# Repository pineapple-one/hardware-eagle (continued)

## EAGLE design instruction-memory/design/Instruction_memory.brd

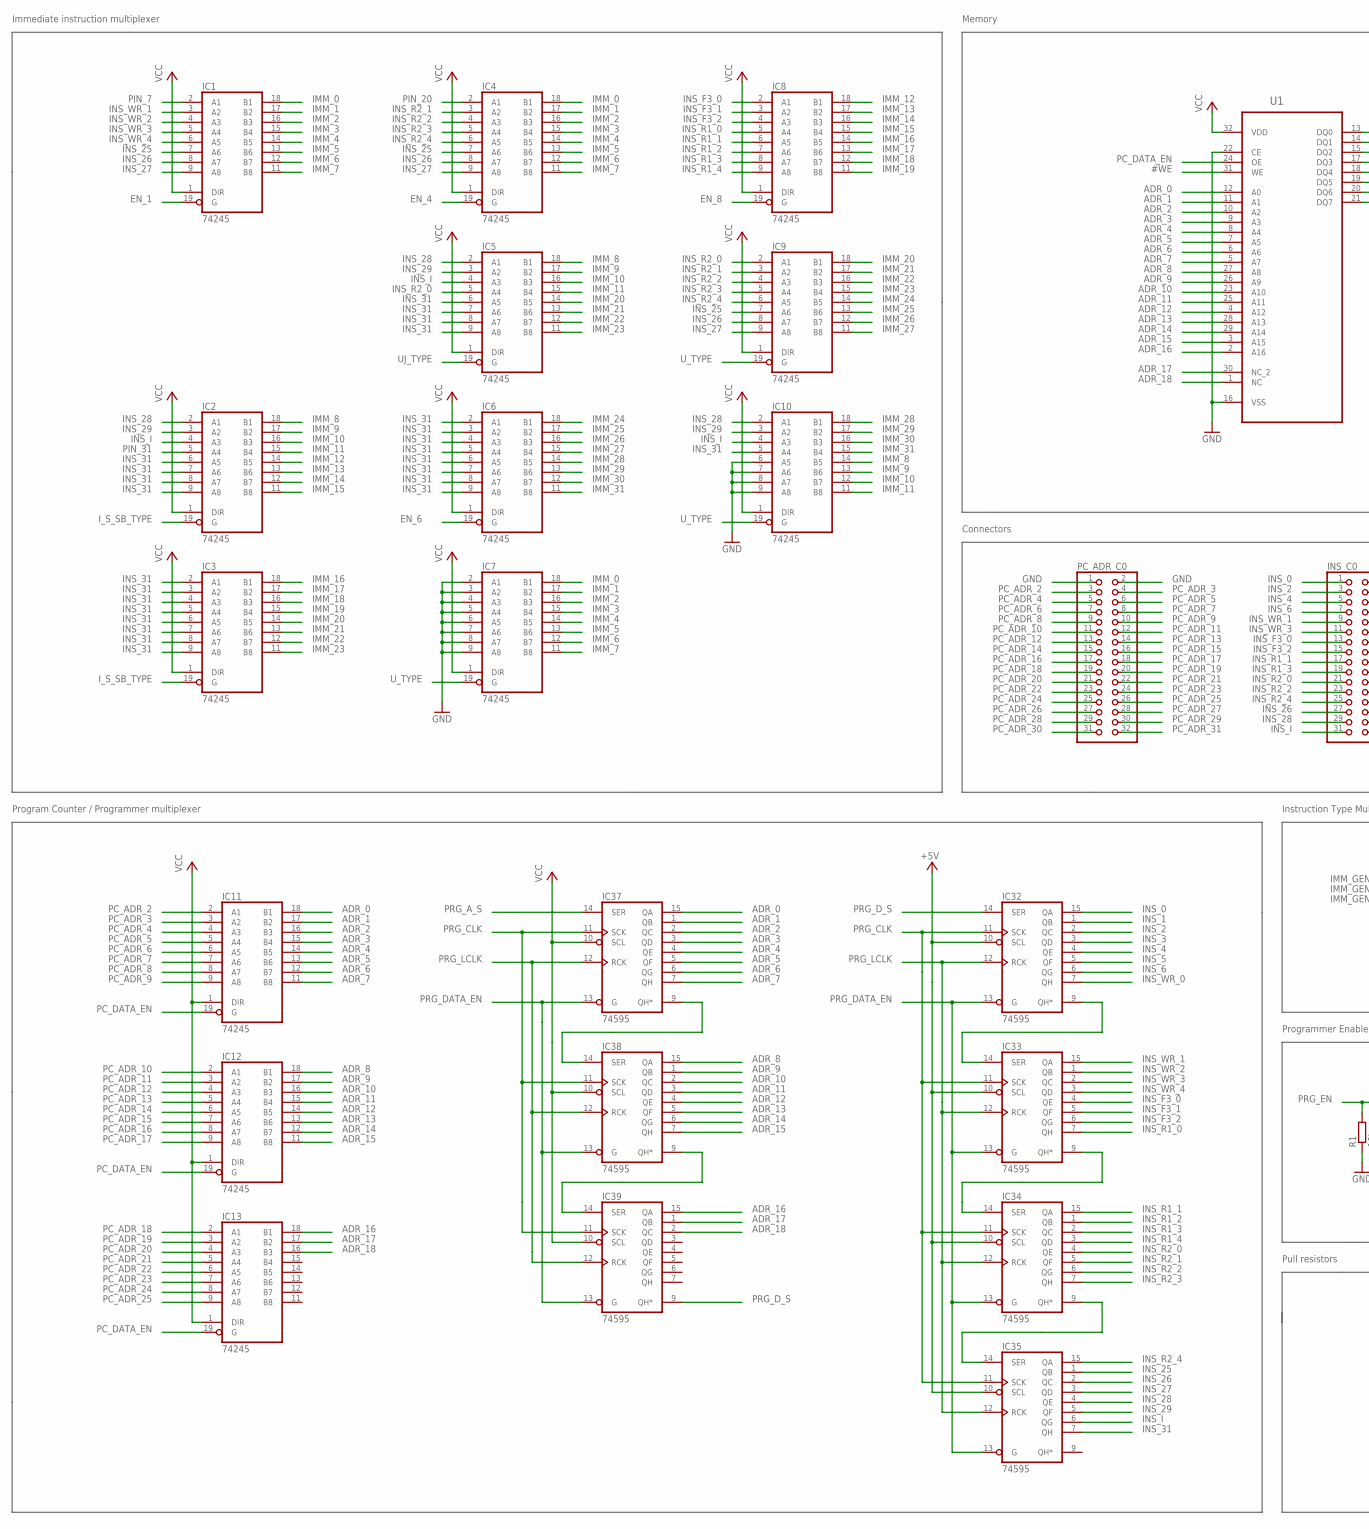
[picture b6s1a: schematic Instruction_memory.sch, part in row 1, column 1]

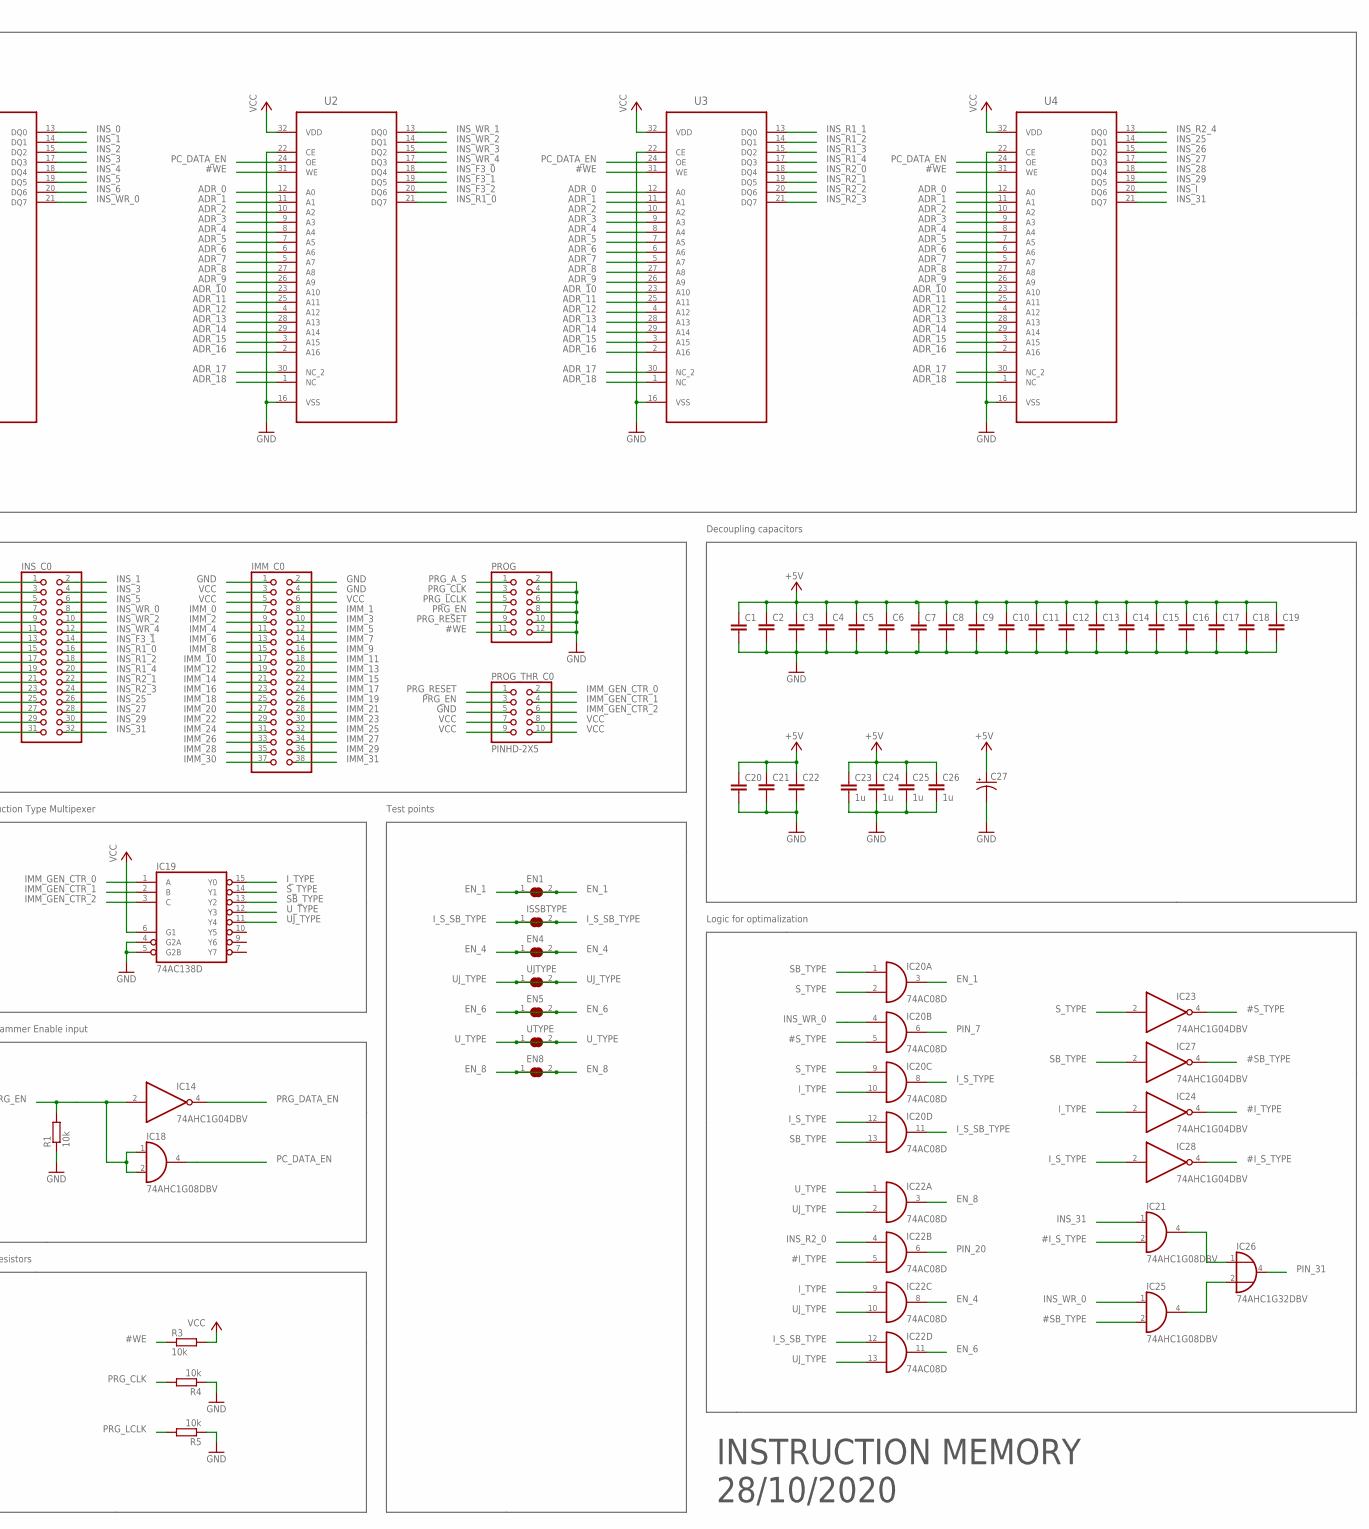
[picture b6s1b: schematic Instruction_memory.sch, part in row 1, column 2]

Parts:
C1, C2, C3, C4, C5, C6, C7, C8, C9, C10, C11, C12, C13, C14, C15, C16, C17, C18, C19, C20, C21, C22: C-EUC0805; C0805
C23, C24, C25, C26: 1u; C0805
C27: CAPACITOR-P153CLV-1010; 153CLV-1010
EN1, EN4, EN5, EN8: SJ
IC1, IC2, IC3, IC4, IC5, IC6, IC7, IC8, IC9, IC10, IC11, IC12, IC13: 74245; TSSOP20
IC14, IC23, IC24, IC27, IC28: 74AHC1G04DBV; SOT23-5
IC18, IC21, IC25: 74AHC1G08DBV; SOT23-5
IC19: 74AC138D; SO16
IC20, IC22: 74AC08D; SO14
IC26: 74AHC1G32DBV; SOT23-5
IC32, IC33, IC34, IC35, IC37, IC38, IC39: 74595; TSSOP16
IMM_C0: PINHD-2X19; 2X19
INS_C0: PINHD-2X16; 2X16
ISSBTYPE: SJ
PC_ADR_C0: PINHD-2X16; 2X16
PROG: PINHD-2X6; 2X06
PROG_THR_C0: PINHD-2X5; 2X05
R1, R3, R4, R5: 10k; R0805
U1, U2, U3, U4: SST39SF010A-70-4I-NHEPLCC32; S32
UJTYPE: SJ
UTYPE: SJ

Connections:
#I_S_TYPE: IC21.2 (I1), IC28.4 (O)
#I_TYPE: IC22.5 (I1), IC24.4 (O)
#SB_TYPE: IC25.2 (I1), IC27.4 (O)
#S_TYPE: IC20.5 (I1), IC23.4 (O)
#WE: PROG.11, R3.1, U1.31 (WE), U2.31 (WE), U3.31 (WE), U4.31 (WE)
ADR_0: IC11.18 (B1), IC37.15 (QA), U1.12 (A0), U2.12 (A0), U3.12 (A0), U4.12 (A0)
ADR_1: IC11.17 (B2), IC37.1 (QB), U1.11 (A1), U2.11 (A1), U3.11 (A1), U4.11 (A1)
ADR_2: IC11.16 (B3), IC37.2 (QC), U1.10 (A2), U2.10 (A2), U3.10 (A2), U4.10 (A2)
ADR_3: IC11.15 (B4), IC37.3 (QD), U1.9 (A3), U2.9 (A3), U3.9 (A3), U4.9 (A3)
ADR_4: IC11.14 (B5), IC37.4 (QE), U1.8 (A4), U2.8 (A4), U3.8 (A4), U4.8 (A4)
ADR_5: IC11.13 (B6), IC37.5 (QF), U1.7 (A5), U2.7 (A5), U3.7 (A5), U4.7 (A5)
ADR_6: IC11.12 (B7), IC37.6 (QG), U1.6 (A6), U2.6 (A6), U3.6 (A6), U4.6 (A6)
ADR_7: IC11.11 (B8), IC37.7 (QH), U1.5 (A7), U2.5 (A7), U3.5 (A7), U4.5 (A7)
ADR_8: IC12.18 (B1), IC38.15 (QA), U1.27 (A8), U2.27 (A8), U3.27 (A8), U4.27 (A8)
ADR_9: IC12.17 (B2), IC38.1 (QB), U1.26 (A9), U2.26 (A9), U3.26 (A9), U4.26 (A9)
ADR_10: IC12.16 (B3), IC38.2 (QC), U1.23 (A10), U2.23 (A10), U3.23 (A10), U4.23 (A10)
ADR_11: IC12.15 (B4), IC38.3 (QD), U1.25 (A11), U2.25 (A11), U3.25 (A11), U4.25 (A11)
ADR_12: IC12.14 (B5), IC38.4 (QE), U1.4 (A12), U2.4 (A12), U3.4 (A12), U4.4 (A12)
ADR_13: IC12.13 (B6), IC38.5 (QF), U1.28 (A13), U2.28 (A13), U3.28 (A13), U4.28 (A13)
ADR_14: IC12.12 (B7), IC38.6 (QG), U1.29 (A14), U2.29 (A14), U3.29 (A14), U4.29 (A14)
ADR_15: IC12.11 (B8), IC38.7 (QH), U1.3 (A15), U2.3 (A15), U3.3 (A15), U4.3 (A15)
ADR_16: IC13.18 (B1), IC39.15 (QA), U1.2 (A16), U2.2 (A16), U3.2 (A16), U4.2 (A16)
ADR_17: IC13.17 (B2), IC39.1 (QB), U1.30 (NC_2), U2.30 (NC_2), U3.30 (NC_2), U4.30 (NC_2)
ADR_18: IC13.16 (B3), IC39.2 (QC), U1.1 (NC), U2.1 (NC), U3.1 (NC), U4.1 (NC)
EN_1: EN1.1, EN1.2, IC1.19 (G), IC20.3 (O)
EN_4: EN4.1, EN4.2, IC4.19 (G), IC22.8 (O)
EN_6: EN5.1, EN5.2, IC6.19 (G), IC22.11 (O)
EN_8: EN8.1, EN8.2, IC8.19 (G), IC22.3 (O)
GND: C1.2, C2.2, C3.2, C4.2, C5.2, C6.2, C7.2, C8.2, C9.2, C10.2, C11.2, C12.2, C13.2, C14.2, C15.2, C16.2, C17.2, C18.2, C19.2, C20.2, C21.2, C22.2, C23.2, C24.2, C25.2, C26.2, C27.-, IC1.10 (GND), IC2.10 (GND), IC3.10 (GND), IC4.10 (GND), IC5.10 (GND), IC6.10 (GND), IC7.2 (A1), IC7.3 (A2), IC7.4 (A3), IC7.5 (A4), IC7.6 (A5), IC7.7 (A6), IC7.8 (A7), IC7.9 (A8), IC7.10 (GND), IC8.10 (GND), IC9.10 (GND), IC10.6 (A5), IC10.7 (A6), IC10.8 (A7), IC10.9 (A8), IC10.10 (GND), IC11.10 (GND), IC12.10 (GND), IC13.10 (GND), IC14.3 (GND), IC18.3 (GND), IC19.4 (G2A), IC19.5 (G2B), IC19.8 (GND), IC20.7 (GND), IC21.3 (GND), IC22.7 (GND), IC23.3 (GND), IC24.3 (GND), IC25.3 (GND), IC26.3 (GND), IC27.3 (GND), IC28.3 (GND), IC32.8 (GND), IC33.8 (GND), IC34.8 (GND), IC35.8 (GND), IC37.8 (GND), IC38.8 (GND), IC39.8 (GND), IMM_C0.1, IMM_C0.2, IMM_C0.4, PC_ADR_C0.1, PC_ADR_C0.2, PROG.2, PROG.4, PROG.6, PROG.8, PROG.10, PROG.12, PROG_THR_C0.5, R1.1, R4.1, R5.1, U1.16 (VSS), U1.22 (CE), U2.16 (VSS), U2.22 (CE), U3.16 (VSS), U3.22 (CE), U4.16 (VSS), U4.22 (CE)
IMM_0: IC1.18 (B1), IC4.18 (B1), IC7.18 (B1), IMM_C0.7
IMM_1: IC1.17 (B2), IC4.17 (B2), IC7.17 (B2), IMM_C0.8
IMM_2: IC1.16 (B3), IC4.16 (B3), IC7.16 (B3), IMM_C0.9
IMM_3: IC1.15 (B4), IC4.15 (B4), IC7.15 (B4), IMM_C0.10
IMM_4: IC1.14 (B5), IC4.14 (B5), IC7.14 (B5), IMM_C0.11
IMM_5: IC1.13 (B6), IC4.13 (B6), IC7.13 (B6), IMM_C0.12
IMM_6: IC1.12 (B7), IC4.12 (B7), IC7.12 (B7), IMM_C0.13
IMM_7: IC1.11 (B8), IC4.11 (B8), IC7.11 (B8), IMM_C0.14
IMM_8: IC2.18 (B1), IC5.18 (B1), IC10.14 (B5), IMM_C0.15
IMM_9: IC2.17 (B2), IC5.17 (B2), IC10.13 (B6), IMM_C0.16
IMM_10: IC2.16 (B3), IC5.16 (B3), IC10.12 (B7), IMM_C0.17
IMM_11: IC2.15 (B4), IC5.15 (B4), IC10.11 (B8), IMM_C0.18
IMM_12: IC2.14 (B5), IC8.18 (B1), IMM_C0.19
IMM_13: IC2.13 (B6), IC8.17 (B2), IMM_C0.20
IMM_14: IC2.12 (B7), IC8.16 (B3), IMM_C0.21
IMM_15: IC2.11 (B8), IC8.15 (B4), IMM_C0.22
IMM_16: IC3.18 (B1), IC8.14 (B5), IMM_C0.23
IMM_17: IC3.17 (B2), IC8.13 (B6), IMM_C0.24
IMM_18: IC3.16 (B3), IC8.12 (B7), IMM_C0.25
IMM_19: IC3.15 (B4), IC8.11 (B8), IMM_C0.26
IMM_20: IC3.14 (B5), IC5.14 (B5), IC9.18 (B1), IMM_C0.27
IMM_21: IC3.13 (B6), IC5.13 (B6), IC9.17 (B2), IMM_C0.28
IMM_22: IC3.12 (B7), IC5.12 (B7), IC9.16 (B3), IMM_C0.29
IMM_23: IC3.11 (B8), IC5.11 (B8), IC9.15 (B4), IMM_C0.30
IMM_24: IC6.18 (B1), IC9.14 (B5), IMM_C0.31
IMM_25: IC6.17 (B2), IC9.13 (B6), IMM_C0.32
IMM_26: IC6.16 (B3), IC9.12 (B7), IMM_C0.33
IMM_27: IC6.15 (B4), IC9.11 (B8), IMM_C0.34
IMM_28: IC6.14 (B5), IC10.18 (B1), IMM_C0.35
IMM_29: IC6.13 (B6), IC10.17 (B2), IMM_C0.36
IMM_30: IC6.12 (B7), IC10.16 (B3), IMM_C0.37
IMM_31: IC6.11 (B8), IC10.15 (B4), IMM_C0.38
IMM_GEN_CTR_0: IC19.1 (A), PROG_THR_C0.2
IMM_GEN_CTR_1: IC19.2 (B), PROG_THR_C0.4
IMM_GEN_CTR_2: IC19.3 (C), PROG_THR_C0.6
INS_0: IC32.15 (QA), INS_C0.1, U1.13 (DQ0)
INS_1: IC32.1 (QB), INS_C0.2, U1.14 (DQ1)
INS_2: IC32.2 (QC), INS_C0.3, U1.15 (DQ2)
INS_3: IC32.3 (QD), INS_C0.4, U1.17 (DQ3)
INS_4: IC32.4 (QE), INS_C0.5, U1.18 (DQ4)
INS_5: IC32.5 (QF), INS_C0.6, U1.19 (DQ5)
INS_6: IC32.6 (QG), INS_C0.7, U1.20 (DQ6)
INS_25: IC1.7 (A6), IC4.7 (A6), IC9.7 (A6), IC35.1 (QB), INS_C0.26, U4.14 (DQ1)
INS_26: IC1.8 (A7), IC4.8 (A7), IC9.8 (A7), IC35.2 (QC), INS_C0.27, U4.15 (DQ2)
INS_27: IC1.9 (A8), IC4.9 (A8), IC9.9 (A8), IC35.3 (QD), INS_C0.28, U4.17 (DQ3)
INS_28: IC2.2 (A1), IC5.2 (A1), IC10.2 (A1), IC35.4 (QE), INS_C0.29, U4.18 (DQ4)
INS_29: IC2.3 (A2), IC5.3 (A2), IC10.3 (A2), IC35.5 (QF), INS_C0.30, U4.19 (DQ5)
INS_31: IC2.6 (A5), IC2.7 (A6), IC2.8 (A7), IC2.9 (A8), IC3.2 (A1), IC3.3 (A2), IC3.4 (A3), IC3.5 (A4), IC3.6 (A5), IC3.7 (A6), IC3.8 (A7), IC3.9 (A8), IC5.6 (A5), IC5.7 (A6), IC5.8 (A7), IC5.9 (A8), IC6.2 (A1), IC6.3 (A2), IC6.4 (A3), IC6.5 (A4), IC6.6 (A5), IC6.7 (A6), IC6.8 (A7), IC6.9 (A8), IC10.5 (A4), IC21.1 (I0), IC35.7 (QH), INS_C0.32, U4.21 (DQ7)
INS_F3_0: IC8.2 (A1), IC33.4 (QE), INS_C0.13, U2.18 (DQ4)
INS_F3_1: IC8.3 (A2), IC33.5 (QF), INS_C0.14, U2.19 (DQ5)
INS_F3_2: IC8.4 (A3), IC33.6 (QG), INS_C0.15, U2.20 (DQ6)
INS_I: IC2.4 (A3), IC5.4 (A3), IC10.4 (A3), IC35.6 (QG), INS_C0.31, U4.20 (DQ6)
INS_R1_0: IC8.5 (A4), IC33.7 (QH), INS_C0.16, U2.21 (DQ7)
INS_R1_1: IC8.6 (A5), IC34.15 (QA), INS_C0.17, U3.13 (DQ0)
INS_R1_2: IC8.7 (A6), IC34.1 (QB), INS_C0.18, U3.14 (DQ1)
INS_R1_3: IC8.8 (A7), IC34.2 (QC), INS_C0.19, U3.15 (DQ2)
INS_R1_4: IC8.9 (A8), IC34.3 (QD), INS_C0.20, U3.17 (DQ3)
INS_R2_0: IC5.5 (A4), IC9.2 (A1), IC22.4 (I0), IC34.4 (QE), INS_C0.21, U3.18 (DQ4)
INS_R2_1: IC4.3 (A2), IC9.3 (A2), IC34.5 (QF), INS_C0.22, U3.19 (DQ5)
INS_R2_2: IC4.4 (A3), IC9.4 (A3), IC34.6 (QG), INS_C0.23, U3.20 (DQ6)
INS_R2_3: IC4.5 (A4), IC9.5 (A4), IC34.7 (QH), INS_C0.24, U3.21 (DQ7)
INS_R2_4: IC4.6 (A5), IC9.6 (A5), IC35.15 (QA), INS_C0.25, U4.13 (DQ0)
INS_WR_0: IC20.4 (I0), IC25.1 (I0), IC32.7 (QH), INS_C0.8, U1.21 (DQ7)
INS_WR_1: IC1.3 (A2), IC33.15 (QA), INS_C0.9, U2.13 (DQ0)
INS_WR_2: IC1.4 (A3), IC33.1 (QB), INS_C0.10, U2.14 (DQ1)
INS_WR_3: IC1.5 (A4), IC33.2 (QC), INS_C0.11, U2.15 (DQ2)
INS_WR_4: IC1.6 (A5), IC33.3 (QD), INS_C0.12, U2.17 (DQ3)
I_S_SB_TYPE: IC2.19 (G), IC3.19 (G), IC20.11 (O), IC22.12 (I0), ISSBTYPE.1, ISSBTYPE.2
I_S_TYPE: IC20.8 (O), IC20.12 (I0), IC28.2 (I)
I_TYPE: IC19.15 (Y0), IC20.10 (I1), IC22.9 (I0), IC24.2 (I)
unnamed: IC21.4 (O), IC26.1 (I0)
unnamed: IC25.4 (O), IC26.2 (I1)
unnamed: IC32.9 (QH*), IC33.14 (SER)
unnamed: IC33.9 (QH*), IC34.14 (SER)
unnamed: IC34.9 (QH*), IC35.14 (SER)
unnamed: IC37.9 (QH*), IC38.14 (SER)
unnamed: IC38.9 (QH*), IC39.14 (SER)
PC_ADR_2: IC11.2 (A1), PC_ADR_C0.3
PC_ADR_3: IC11.3 (A2), PC_ADR_C0.4
PC_ADR_4: IC11.4 (A3), PC_ADR_C0.5
PC_ADR_5: IC11.5 (A4), PC_ADR_C0.6
PC_ADR_6: IC11.6 (A5), PC_ADR_C0.7
PC_ADR_7: IC11.7 (A6), PC_ADR_C0.8
PC_ADR_8: IC11.8 (A7), PC_ADR_C0.9
PC_ADR_9: IC11.9 (A8), PC_ADR_C0.10
PC_ADR_10: IC12.2 (A1), PC_ADR_C0.11
PC_ADR_11: IC12.3 (A2), PC_ADR_C0.12
PC_ADR_12: IC12.4 (A3), PC_ADR_C0.13
PC_ADR_13: IC12.5 (A4), PC_ADR_C0.14
PC_ADR_14: IC12.6 (A5), PC_ADR_C0.15
PC_ADR_15: IC12.7 (A6), PC_ADR_C0.16
PC_ADR_16: IC12.8 (A7), PC_ADR_C0.17
PC_ADR_17: IC12.9 (A8), PC_ADR_C0.18
PC_ADR_18: IC13.2 (A1), PC_ADR_C0.19
PC_ADR_19: IC13.3 (A2), PC_ADR_C0.20
PC_ADR_20: IC13.4 (A3), PC_ADR_C0.21
PC_ADR_21: IC13.5 (A4), PC_ADR_C0.22
PC_ADR_22: IC13.6 (A5), PC_ADR_C0.23
PC_ADR_23: IC13.7 (A6), PC_ADR_C0.24
PC_ADR_24: IC13.8 (A7), PC_ADR_C0.25
PC_ADR_25: IC13.9 (A8), PC_ADR_C0.26
PC_ADR_26: PC_ADR_C0.27
PC_ADR_27: PC_ADR_C0.28
PC_ADR_28: PC_ADR_C0.29
PC_ADR_29: PC_ADR_C0.30
PC_ADR_30: PC_ADR_C0.31
PC_ADR_31: PC_ADR_C0.32
PC_DATA_EN: IC11.19 (G), IC12.19 (G), IC13.19 (G), IC18.4 (O), U1.24 (OE), U2.24 (OE), U3.24 (OE), U4.24 (OE)
PIN_7: IC1.2 (A1), IC20.6 (O)
PIN_20: IC4.2 (A1), IC22.6 (O)
PIN_31: IC2.5 (A4), IC26.4 (O)
PRG_A_S: IC37.14 (SER), PROG.1
PRG_CLK: IC32.11 (SCK), IC33.11 (SCK), IC34.11 (SCK), IC35.11 (SCK), IC37.11 (SCK), IC38.11 (SCK), IC39.11 (SCK), PROG.3, R4.2
PRG_DATA_EN: IC14.4 (O), IC32.13 (G), IC33.13 (G), IC34.13 (G), IC35.13 (G), IC37.13 (G), IC38.13 (G), IC39.13 (G)
PRG_D_S: IC32.14 (SER), IC39.9 (QH*)
PRG_EN: IC14.2 (I), IC18.1 (I0), IC18.2 (I1), PROG.7, PROG_THR_C0.3, R1.2
PRG_LCLK: IC32.12 (RCK), IC33.12 (RCK), IC34.12 (RCK), IC35.12 (RCK), IC37.12 (RCK), IC38.12 (RCK), IC39.12 (RCK), PROG.5, R5.2
PRG_RESET: PROG.9, PROG_THR_C0.1
SB_TYPE: IC19.13 (Y2), IC20.1 (I0), IC20.13 (I1), IC27.2 (I)
S_TYPE: IC19.14 (Y1), IC20.2 (I1), IC20.9 (I0), IC23.2 (I)
UJ_TYPE: IC5.19 (G), IC19.11 (Y4), IC22.2 (I1), IC22.10 (I1), IC22.13 (I1), UJTYPE.1, UJTYPE.2
U_TYPE: IC7.19 (G), IC9.19 (G), IC10.19 (G), IC19.12 (Y3), IC22.1 (I0), UTYPE.1, UTYPE.2
VCC: C1.1, C2.1, C3.1, C4.1, C5.1, C6.1, C7.1, C8.1, C9.1, C10.1, C11.1, C12.1, C13.1, C14.1, C15.1, C16.1, C17.1, C18.1, C19.1, C20.1, C21.1, C22.1, C23.1, C24.1, C25.1, C26.1, C27.+, IC1.1 (DIR), IC1.20 (VCC), IC2.1 (DIR), IC2.20 (VCC), IC3.1 (DIR), IC3.20 (VCC), IC4.1 (DIR), IC4.20 (VCC), IC5.1 (DIR), IC5.20 (VCC), IC6.1 (DIR), IC6.20 (VCC), IC7.1 (DIR), IC7.20 (VCC), IC8.1 (DIR), IC8.20 (VCC), IC9.1 (DIR), IC9.20 (VCC), IC10.1 (DIR), IC10.20 (VCC), IC11.1 (DIR), IC11.20 (VCC), IC12.1 (DIR), IC12.20 (VCC), IC13.1 (DIR), IC13.20 (VCC), IC14.5 (VCC), IC18.5 (VCC), IC19.6 (G1), IC19.16 (VCC), IC20.14 (VCC), IC21.5 (VCC), IC22.14 (VCC), IC23.5 (VCC), IC24.5 (VCC), IC25.5 (VCC), IC26.5 (VCC), IC27.5 (VCC), IC28.5 (VCC), IC32.10 (SCL), IC32.16 (VCC), IC33.10 (SCL), IC33.16 (VCC), IC34.10 (SCL), IC34.16 (VCC), IC35.10 (SCL), IC35.16 (VCC), IC37.10 (SCL), IC37.16 (VCC), IC38.10 (SCL), IC38.16 (VCC), IC39.10 (SCL), IC39.16 (VCC), IMM_C0.3, IMM_C0.5, IMM_C0.6, PROG_THR_C0.7, PROG_THR_C0.8, PROG_THR_C0.9, PROG_THR_C0.10, R3.2, U1.32 (VDD), U2.32 (VDD), U3.32 (VDD), U4.32 (VDD)

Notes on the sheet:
Decoupling capacitors
Memory
Instruction Type Multipexer
Pull resistors
Connectors
Logic for optimalization
Immediate instruction multiplexer
Program Counter / Programmer multiplexer
Programmer Enable input
Test points
INSTRUCTION MEMORY 28/10/2020

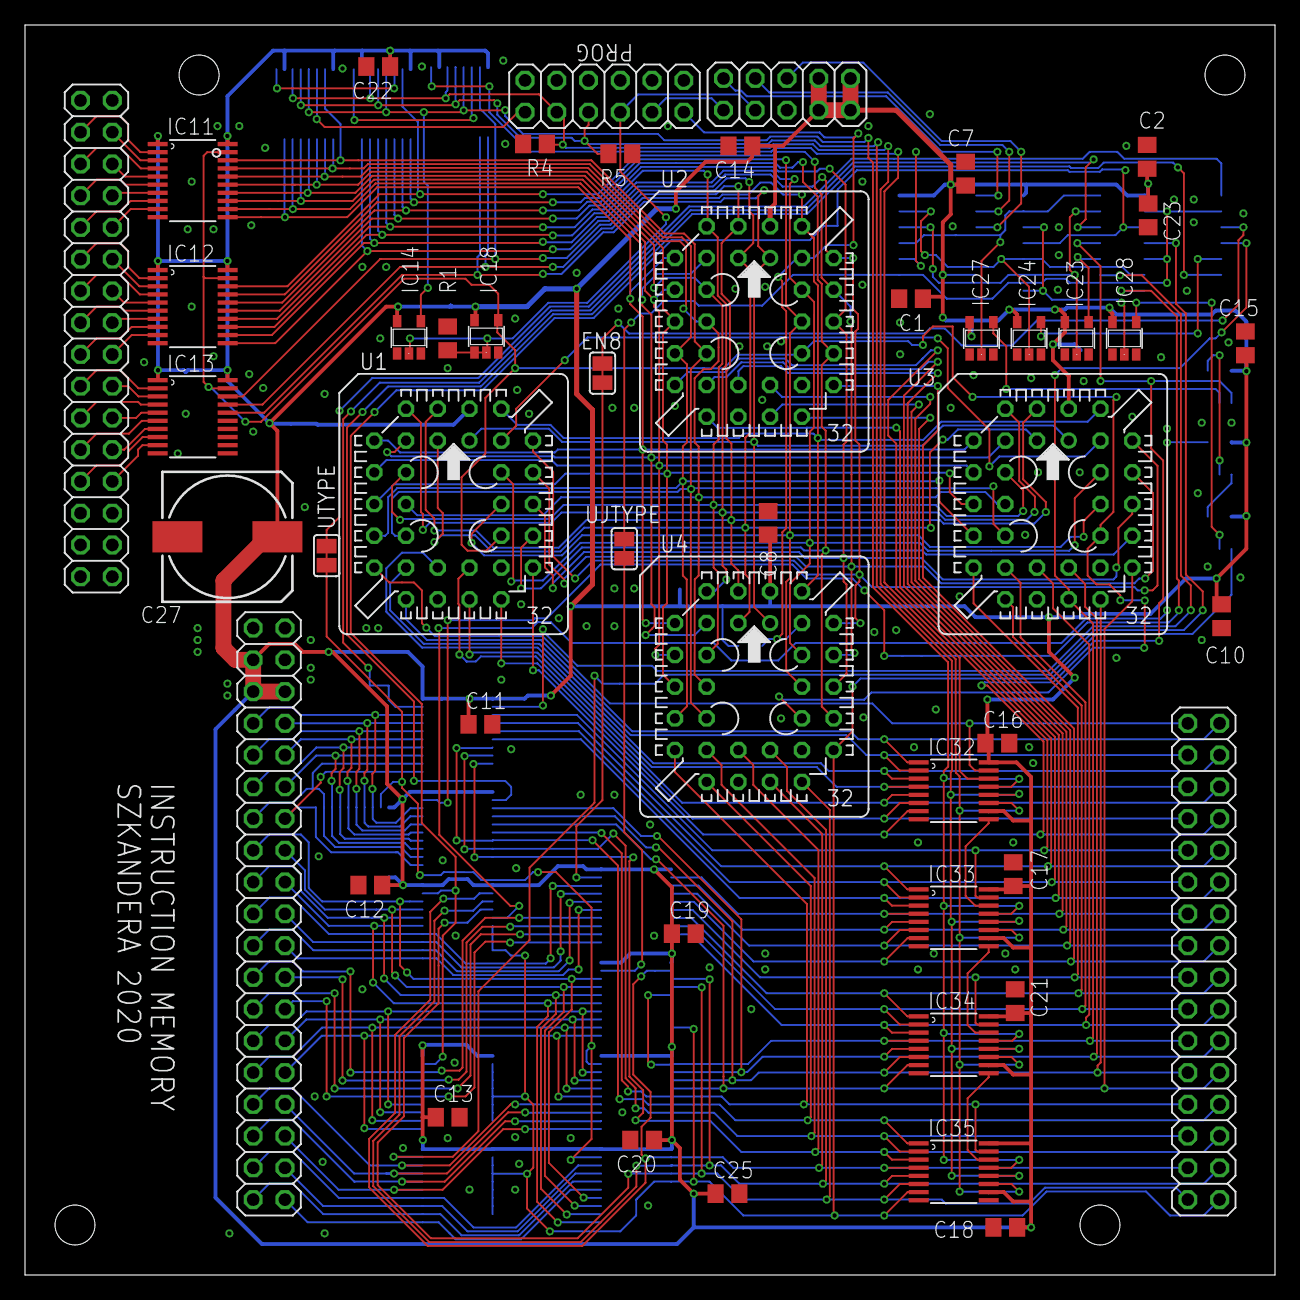
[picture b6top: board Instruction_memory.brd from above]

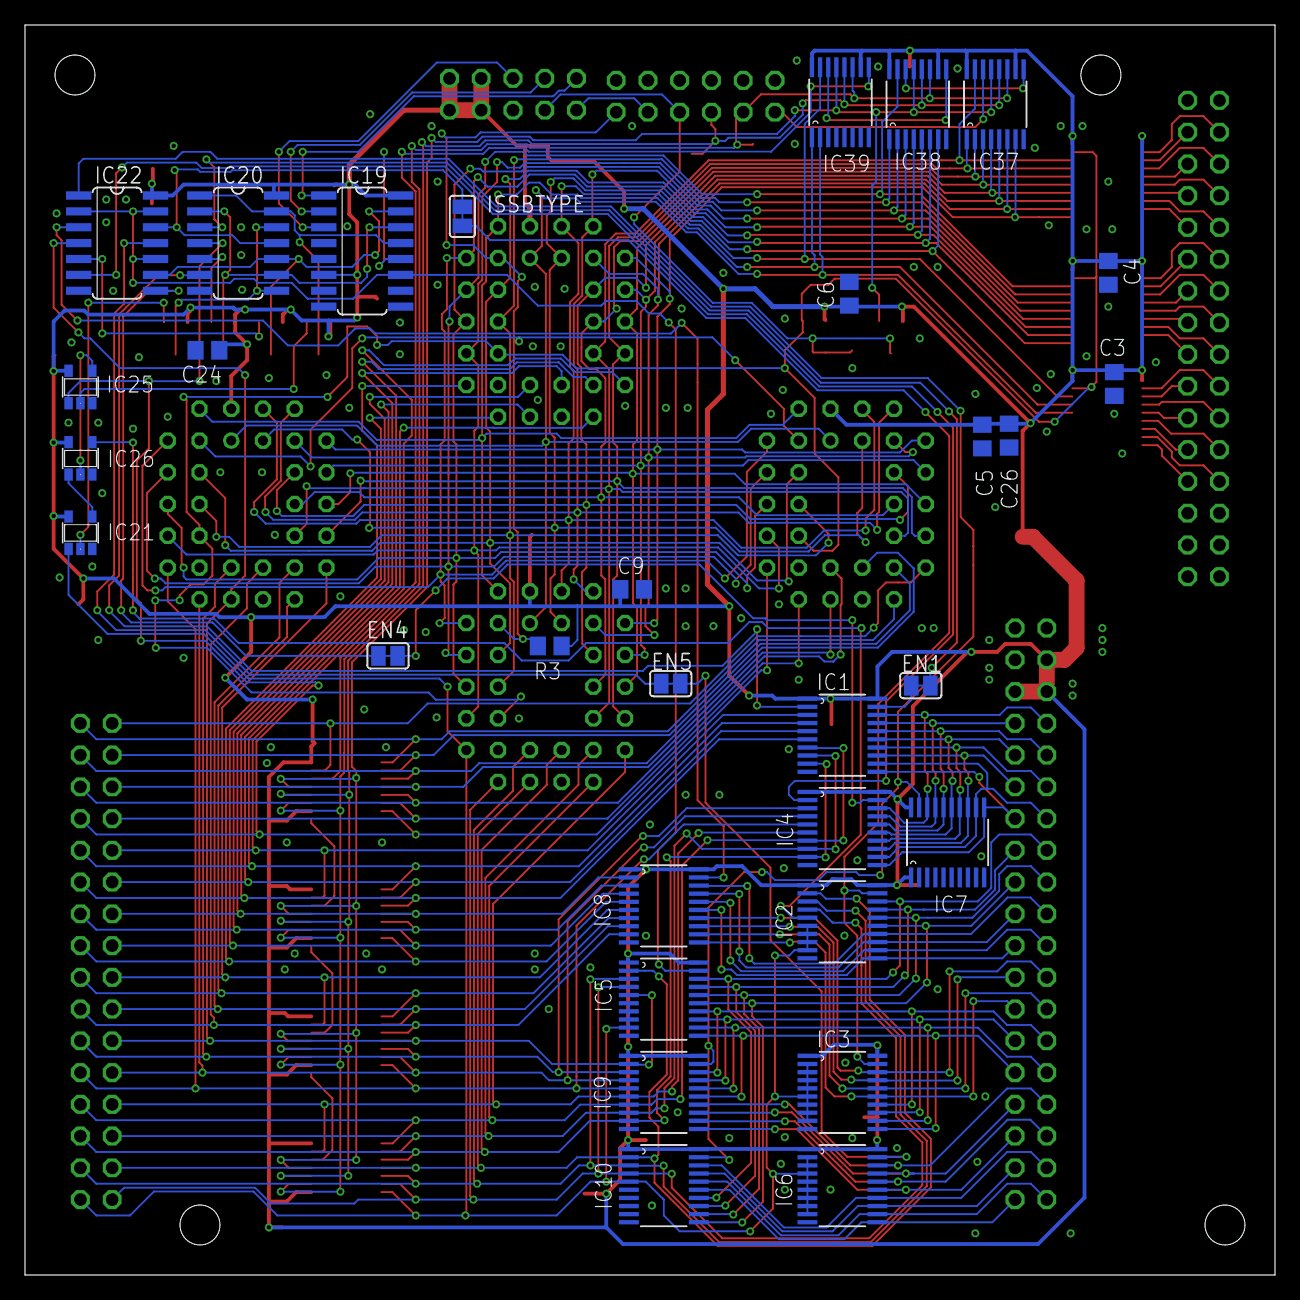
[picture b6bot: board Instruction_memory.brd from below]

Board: 2 copper layers, 100.0 x 100.0 mm, 79 parts (31 on the bottom side), 146 nets.
